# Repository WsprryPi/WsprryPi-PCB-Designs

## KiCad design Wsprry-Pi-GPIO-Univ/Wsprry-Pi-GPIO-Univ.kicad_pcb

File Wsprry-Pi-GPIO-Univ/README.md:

# Wsprry Pi GPIO Board

GPIO transmission board.

## Project files

Open [Wsprry-Pi-GPIO-Univ.kicad_pro](Wsprry-Pi-GPIO-Univ.kicad_pro) in KiCad 10.0.1 or newer. The [schematic PDF](Wsprry-Pi-GPIO-Univ.pdf) is a reference export; the KiCad sources are authoritative.

The [project libraries](libraries/README.md) contain every symbol and footprint used by the design, plus available 3D models. Keep the `libraries/` folder and library tables with the project; their `${KIPRJMOD}` paths resolve within this directory. Library documentation covers connector options, model limitations, sources, and licenses.

## Assembly

C11 is [Panasonic EEEFK1V470P, 47 µF / 35 V](https://www.lcsc.com/product-detail/C178565.html), matching the `C178565` purchasing field, schematic value, and PCB value. Its local footprint uses KiCad's generic `CP_Elec_6.3x5.8` STEP model for visualization; verify the selected part and assembled height mechanically rather than treating the model as physical-fit evidence.

J83 is the locally stored Adafruit 1865 edge-launch SMA connector, with signal on pin 1 and ground on pin 2. It is hand-soldered and excluded from the BOM and position files. The nearby RF route was revised and the conflicting local fence vias were removed; the surrounding ground-via fence remains in place.

Headers J11, J21, J81, and J82 remain part of the electrical design but are excluded from the BOM. Treat them as separately supplied assembly hardware.

## Validation

The design was checked with KiCad 10.0.1 after the edge-connector and 3D-model changes. Run ERC and DRC again after later design edits and before producing manufacturing files.

- ERC: no errors and 1 unconnected-wire-endpoint warning.
- DRC: zero violations, unconnected pads, or schematic-parity errors.

The macOS `kicad-cli pcb drc` launcher aborted in KiCad's UI-registration path during this review, so the reported DRC result comes from the native PCB Editor with zone refill and schematic parity enabled. Board parsing, STEP export, and 3D rendering completed successfully.

The project settings include ignored ERC/DRC categories. These checks do not establish assembly fit or electrical/RF performance. Treat the design as untested until revision-specific physical validation is documented. See the [repository conventions](../README.md) and [validation requirements](../CONTRIBUTING.md).

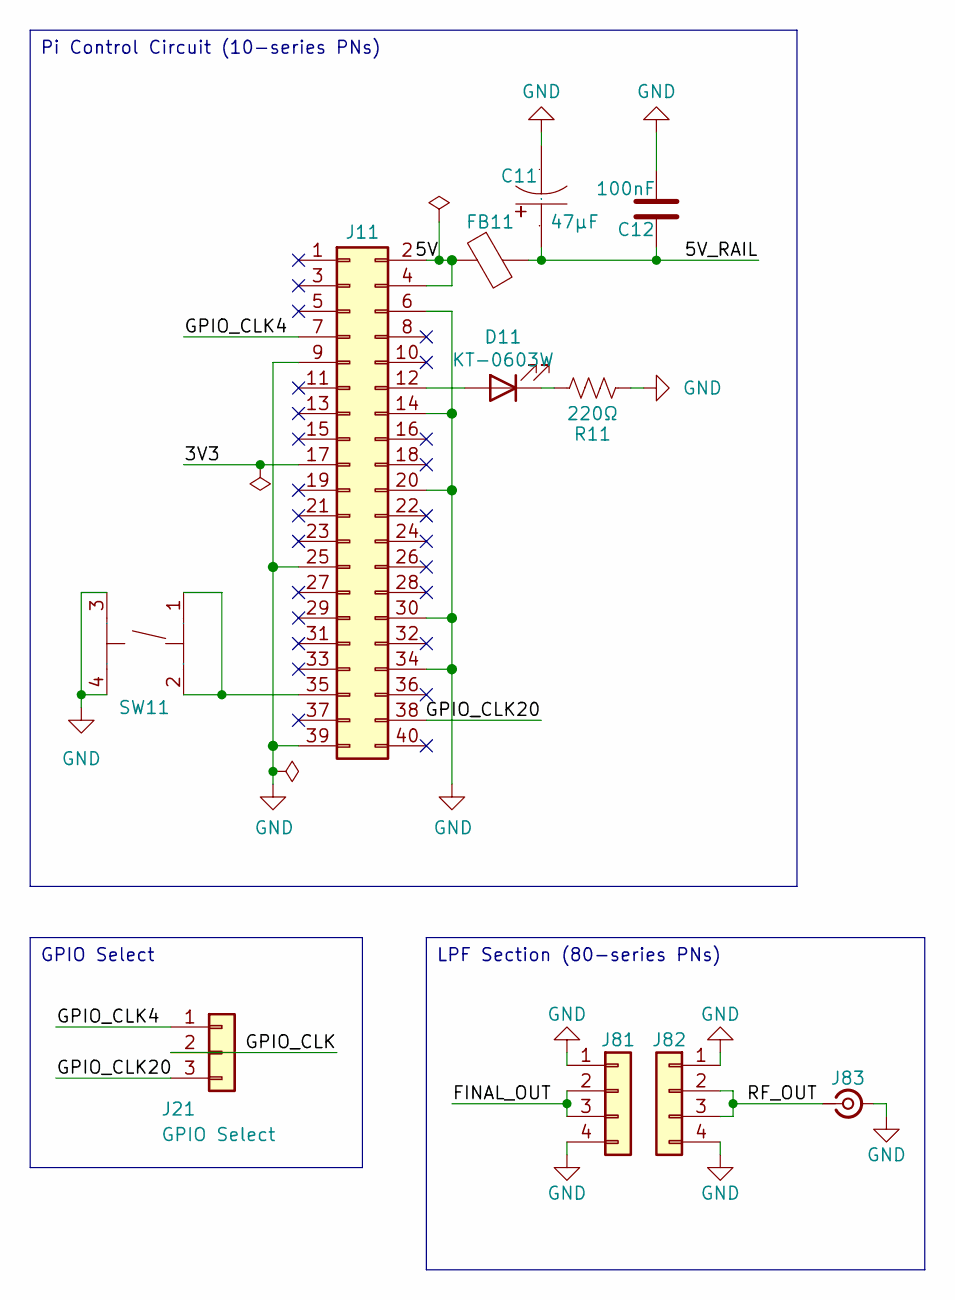
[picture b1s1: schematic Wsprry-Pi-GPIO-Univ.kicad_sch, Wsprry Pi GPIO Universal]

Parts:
C11: 47µF; CAP-SMD_BD6.3-L6.6-W6.6-FD; LCSC_PART C178565
C12: 100nF; C_0603_1608Metric; LCSC_PART C14663
D11: KT-0603W; LED_0603_1608Metric; LCSC_PART C2286
FB11: 600Ω@100MHz; L_0603_1608Metric; LCSC_PART C107335
J11: GPIO; PinSocket_2x20_P2.54mm_Vertical; LCSC_PART C2977589
J21: GPIO Select; PinHeader_1x03_P1.00mm_Vertical
J81, J82: Conn_01x04; PinSocket_1x04_P2.54mm_Vertical; LCSC_PART C2718488
J83: SMA_Adafruit_1865; SMA_Adafruit_1865_EdgeMount; MPN 1865
R11: 220Ω; R_0603_1608Metric; LCSC_PART C22962
SW11: Switch; SW-SMD_4P-L5.1-W5.1-P3.70-LS6.5-TL_H1.5; LCSC_PART C318884

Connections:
/3V3: J11.17
/5V: FB11.1, J11.2, J11.4
/5V_RAIL: C11.1, C12.1, FB11.2
/FINAL_OUT: J81.2, J81.3
/GPIO_CLK: J21.2
/GPIO_CLK4: J11.7, J21.1
/GPIO_CLK20: J11.38, J21.3
/RF_OUT: J82.2, J82.3, J83.1 (In)
GND: C11.2, C12.2, J11.6, J11.9, J11.14, J11.20, J11.25, J11.30, J11.34, J11.39, J81.1, J81.4, J82.1, J82.4, J83.2 (GND), R11.1, SW11.3 (C), SW11.4 (D)
unnamed: D11.2 (A), J11.12
unnamed: D11.1 (K), R11.2
unnamed: J11.35, SW11.1 (A), SW11.2 (B)

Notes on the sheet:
GPIO Select
Pi Control Circuit (10-series PNs)
LPF Section (80-series PNs)

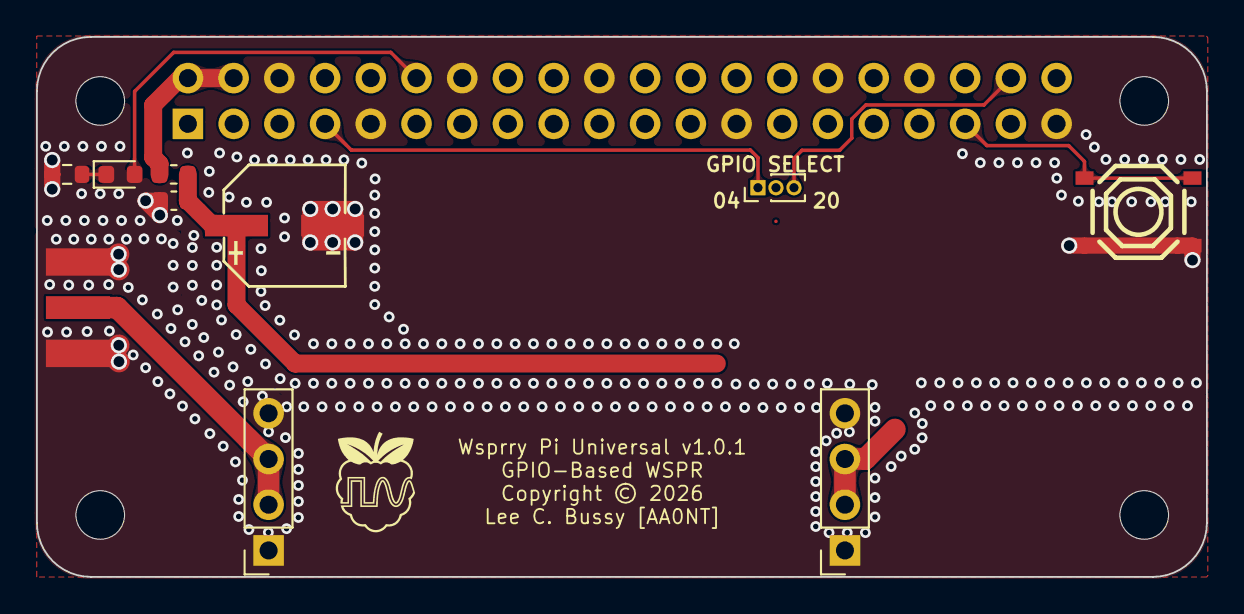
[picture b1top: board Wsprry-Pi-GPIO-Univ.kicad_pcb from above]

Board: 2 copper layers, 65.0 x 30.0 mm, 15 parts (1 on the bottom side), 10 nets.

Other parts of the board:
MH1, MH2, MH3, MH4: MountingHole_2.7mm_M2.5

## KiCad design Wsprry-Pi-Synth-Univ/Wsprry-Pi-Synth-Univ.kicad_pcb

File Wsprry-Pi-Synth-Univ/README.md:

# Wsprry Pi Synth Board

Si5351-synthesized transmission board.

## Project files

Open [Wsprry-Pi-Synth-Univ.kicad_pro](Wsprry-Pi-Synth-Univ.kicad_pro) in KiCad 10.0.1 or newer. The [schematic PDF](Wsprry-Pi-Synth-Univ.pdf) is a reference export; the KiCad sources are authoritative.

The [project libraries](libraries/README.md) contain every symbol and footprint used by the design, plus available 3D models. Keep the `libraries/` folder and library tables with the project; their `${KIPRJMOD}` paths resolve within this directory. Library documentation covers connector options, model limitations, sources, and licenses.

## Assembly

**Resolve C11 before ordering:** the schematic and PCB specify 100 µF, but the `C178565` purchasing fields select [Panasonic EEEFK1V470P, 47 µF / 35 V](https://www.lcsc.com/product-detail/C178565.html). The local symbol default describes the 47 µF part.

J83 is a through-hole BWSMA-KWE-Z001 connector ([LCSC C496551](https://www.lcsc.com/product-detail/C496551.html)), with signal on pin 5 and ground on pins 1–4. The local Adafruit 1865 edge-launch option uses signal pin 1 and ground pin 2; using it requires schematic pin mapping and PCB routing changes.

## Validation

The validation baseline is source revision `bc5cba8`, checked with KiCad 10.0.1. Run ERC and DRC again after design edits and before producing manufacturing files.

- ERC: no errors and 2 unconnected-wire-endpoint warnings.
- DRC: zero violations, unconnected pads, or footprint errors.

The project settings include ignored ERC/DRC categories. These checks do not establish assembly fit or electrical/RF performance. Treat the design as untested until revision-specific physical validation is documented. See the [repository conventions](../README.md) and [validation requirements](../CONTRIBUTING.md).

## Design considerations

[Optional GPS frequency calibration for Pi and Pico](../design/GPS-FREQUENCY-CALIBRATION.md) records the selected LS7366R counter and a proposed common 3.3 V circuit for Pi and Pico. It describes CLK2 measurement against GPS PPS, SPI capture readout, benefits, standalone operation and holdover, and an optional external GPSDO reference. The circuit has not been implemented or physically validated.

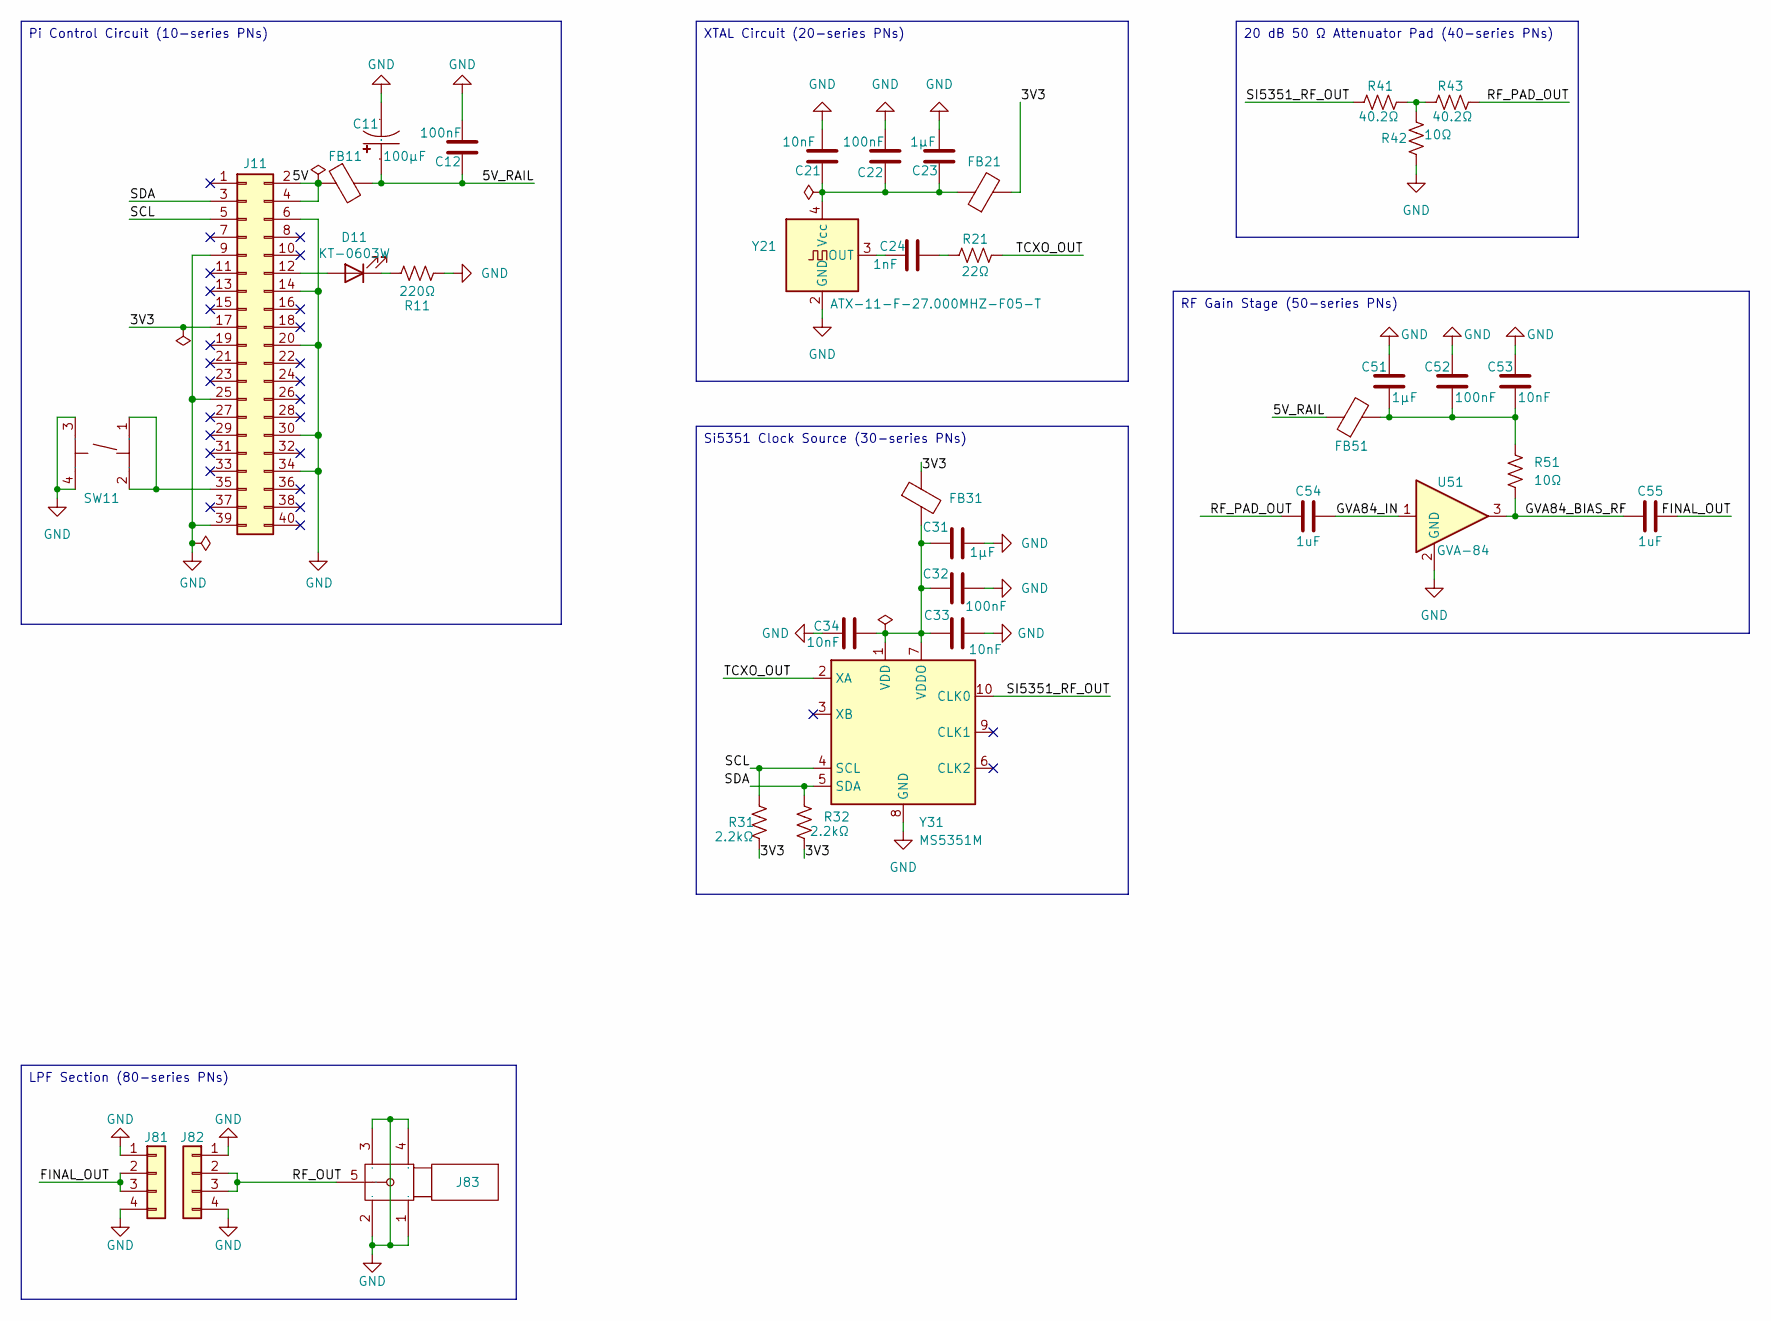
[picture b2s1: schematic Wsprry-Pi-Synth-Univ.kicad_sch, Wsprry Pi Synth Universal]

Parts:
C11: 100µF; CAP-SMD_BD6.3-L6.6-W6.6-FD; LCSC_PART C178565
C12: 100nF; C_0603_1608Metric; LCSC_PART C14663
C21, C33, C34, C53: 10nF; C_0402_1005Metric; LCSC_PART C15195
C22, C32, C52: 100nF; C_0402_1005Metric; LCSC_PART C307331
C23, C31, C51: 1µF; C_0603_1608Metric; LCSC_PART C15849
C24: 1nF; C_0402_1005Metric; LCSC_PART C1523
C54, C55: 1uF; C_0805_2012Metric; LCSC_PART C28323
D11: KT-0603W; LED_0603_1608Metric; LCSC_PART C2286
FB11, FB21, FB31, FB51: 600Ω@100MHz; L_0603_1608Metric; LCSC_PART C107335
J11: GPIO; PinSocket_2x20_P2.54mm_Vertical; LCSC_PART C2977589
J81, J82: Conn_01x04; PinSocket_1x04_P2.54mm_Vertical; LCSC_PART C2718488
J83: SMA; SMA-TH_BWSMA-KWE-Z001; Manufacturer Part BWSMA-KWE-Z001; LCSC_PART C496551
R11: 220Ω; R_0603_1608Metric; LCSC_PART C22962
R21: 22Ω; R_0402_1005Metric; LCSC_PART C25092
R31, R32: 2.2kΩ; R_0402_1005Metric; LCSC_PART C25879
R41, R43: 40.2Ω; R_0603_1608Metric; LCSC_PART C705775
R42: 10Ω; R_0603_1608Metric; LCSC_PART C217691
R51: 10Ω; R_0805_2012Metric; LCSC_PART C17415
SW11: Switch; SW-SMD_4P-L5.1-W5.1-P3.70-LS6.5-TL_H1.5; LCSC_PART C318884
U51: GVA-84; SOT-89-3; LCSC_PART C5445191
Y21: ATX-11-F-27.000MHZ-F05-T; Oscillator_SMD_SeikoEpson_TG2520SMN-xxx-xxxxxx-4Pin_2.5x2.0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; LCSC_PART C6508794
Y31: MS5351M; MSOP-10_3x3mm_P0.5mm; LCSC_PART C1509083

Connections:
/3V3: FB21.2, FB31.1, J11.17, R31.1, R32.1
/5V: FB11.1, J11.2, J11.4
/5V_RAIL: C11.1, C12.1, FB11.2, FB51.1
/FINAL_OUT: C55.2, J81.2, J81.3
/GVA84_BIAS_RF: C55.1, R51.2, U51.3
/GVA84_IN: C54.2, U51.1
/RF_OUT: J82.2, J82.3, J83.5
/RF_PAD_OUT: C54.1, R43.2
/SCL: J11.5, R31.2, Y31.4 (SCL)
/SDA: J11.3, R32.2, Y31.5 (SDA)
/SI5351_RF_OUT: R41.1, Y31.10 (CLK0)
/TCXO_OUT: R21.1, Y31.2 (XA)
GND: C11.2, C12.2, C21.1, C22.1, C23.1, C31.1, C32.2, C33.1, C34.1, C51.2, C52.2, C53.2, J11.6, J11.9, J11.14, J11.20, J11.25, J11.30, J11.34, J11.39, J81.1, J81.4, J82.1, J82.4, J83.1, J83.2, J83.3, J83.4, R11.1, R42.1, SW11.3 (C), SW11.4 (D), U51.2 (GND), Y21.2 (GND), Y31.8 (GND)
unnamed: C24.2, R21.2
unnamed: C51.1, C52.1, C53.1, FB51.2, R51.1
unnamed: D11.2 (A), J11.12
unnamed: D11.1 (K), R11.2
unnamed: J11.35, SW11.1 (A), SW11.2 (B)
unnamed: R41.2, R42.2, R43.1
unnamed: C24.1, Y21.3 (OUT)
unnamed: C21.2, C22.2, C23.2, FB21.1, Y21.4 (Vcc)
unnamed: C31.2, C32.1, C33.2, C34.2, FB31.2, Y31.1 (VDD), Y31.7 (VDDO)

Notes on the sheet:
20 dB 50 Ω Attenuator Pad (40-series PNs)
Pi Control Circuit (10-series PNs)
RF Gain Stage (50-series PNs)
Si5351 Clock Source (30-series PNs)
LPF Section (80-series PNs)
XTAL Circuit (20-series PNs)

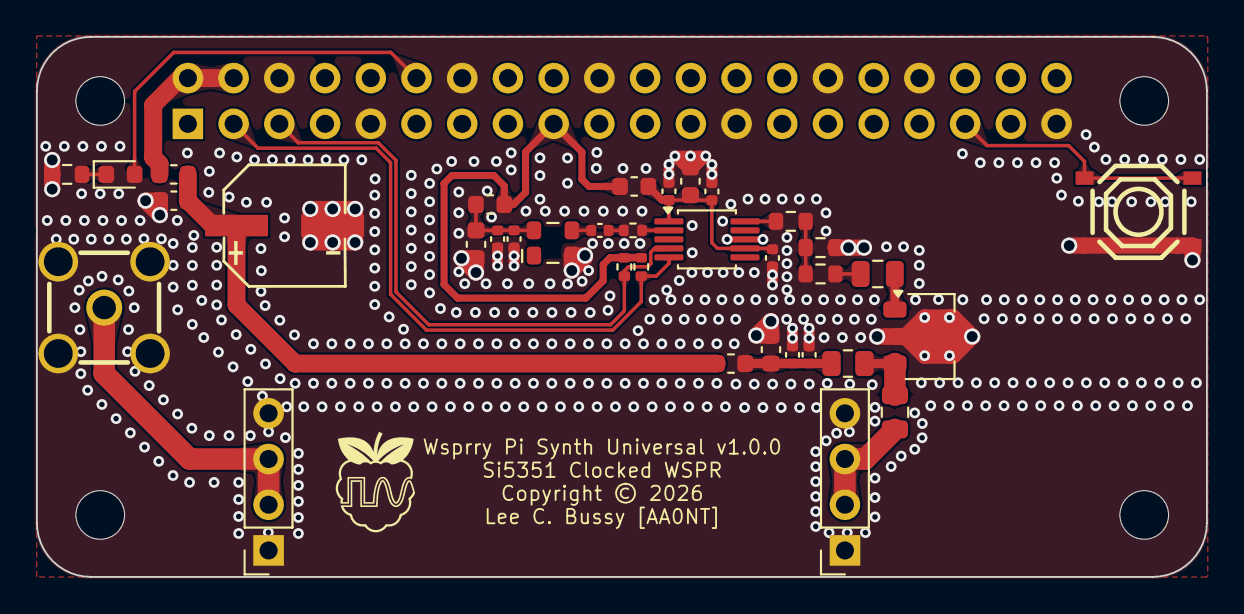
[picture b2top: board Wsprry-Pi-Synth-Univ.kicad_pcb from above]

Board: 2 copper layers, 65.0 x 30.0 mm, 40 parts (1 on the bottom side), 22 nets.

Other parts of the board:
MH1, MH2, MH3, MH4: MountingHole_2.7mm_M2.5

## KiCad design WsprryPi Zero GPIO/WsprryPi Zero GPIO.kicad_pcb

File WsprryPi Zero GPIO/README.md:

# WsprryPi Zero GPIO

A KiCad 10 project initialized from the `RPi Zero HAT` template for WsprryPi GPIO development. It provides the Raspberry Pi Zero-size uHAT geometry, a complete 40-pin GPIO interface, a selectable underside socket model, a socket purchasing item, and independent local libraries.

The schematic and routed two-layer PCB contain the first implementation pass of the 5 V RF amplifier, load-switch circuit, GPIO selection header, LPF interface, and edge-launch SMA output. The design intentionally omits an identification EEPROM and leaves ID_SD and ID_SC unused. Placement and routing are saved, but the board has not been fabricated or physically qualified.

**Cost redesign in progress:** the saved two-transformer LTC6432-15 implementation is too expensive and is no longer the forward design choice. See the [single-BS170 redesign proposal](BS170-REDESIGN-PROPOSAL.md) for the lower-cost candidate and its band-dependent power limits. The proposal has not been applied to the KiCad sources; this routed board remains unsuitable for ordering.

The saved 5 V LTC6432-15 amplifier architecture, its original RF estimate, first-pass BOM, and remaining implementation decisions are recorded in [AMPLIFIER-DESIGN.md](AMPLIFIER-DESIGN.md). It is a new design and does not inherit the earlier 1 W amplifier requirements.

> **Order status: Not ready for order.** The saved implementation uses two Coilcraft `WBC2-1TLC` transformers and an LTC6432-15; it has been rejected on cost grounds. The transformer substitution and the board's electrical/RF performance have not been qualified. The WBC2-1TLC data sheet begins its specified frequency range at 0.2 MHz, above this project's 135 kHz lower target. Do not submit the saved board for fabrication or assembly as the lower-cost design.

## Develop this HAT project

1. Open `WsprryPi Zero GPIO.kicad_pro` in KiCad 10 and review the saved schematic and routed board together.
2. Review the [BS170 redesign proposal](BS170-REDESIGN-PROPOSAL.md) and resolve its open circuit, power, sourcing, and compliance decisions before changing the KiCad sources.
3. After any design change, update the PCB from the schematic as needed, refill copper zones, and rerun ERC and DRC before reviewing the resulting diff.

This project has independent copies of the design files, symbol library, footprint library, and STEP model. Changes here do not update `RPi Zero HAT`, and later template changes do not update this project.

## Schematic block numbering

The schematic is arranged as five boxed functional sections. Circuit parts within those blocks use reference numbers from their section's decade; the prefix distinguishes component types, so a suffix may be reused across types. A few interface and board-only parts retain special references as documented below. Connections within each section are drawn conventionally with wires and explicit branch junctions; net labels are reserved primarily for interfaces between sections and ground references.

| Series | Functional block | References |
| --- | --- | --- |
| 10 | Raspberry Pi HAT interface, GPIO indicator, GPIO-selection header, and socket purchasing item | `U10`, `D11`, `R11`, `J11`, `J12` |
| 20 | GPIO damping, DC blocking, boot-state pull-down, and input transformer | `R20`, `C21`, `R21`, `T21` |
| 30 | LTC6432-15 amplifier, coupling, feedback, noise filtering, and bypassing | `C30`–`C37`, `U31` |
| 40 | Output transformer and grouped J81/J82 LPF interface | `T41`, `J41` |
| 50 | TPS22918 switched 5 V amplifier supply | `U50`, `C51`, `R52`, `C53`, `R54`, `C55` |

J1 is the hand-soldered edge-launch output connector, and H1 is the board-only 3D socket representation; those references sit outside the functional-decade annotation convention. SW11 is the software shutdown-request button in the 10-series. J12 permits GPIO4 or GPIO20 to be jumpered onto `GPIO_RF`. GPIO23 is the active-high `AMP_EN` control, and SW11 grounds GPIO26 for software to detect. GPIO drive-strength selection remains coarse and experimental rather than a calibrated power control.

## Mechanical interface

Coordinates below use the upper-left corner of the 65 × 30 mm board envelope as `(0, 0)`.

| Item | Geometry |
| --- | --- |
| Board envelope | 65 × 30 mm; 1.6 mm thickness; two copper layers |
| Outer corners | 3 mm radius |
| Mounting holes | Four 2.75 mm non-plated holes at `(3.5, 3.5)`, `(61.5, 3.5)`, `(3.5, 26.5)`, and `(61.5, 26.5)` mm |
| Mounting-hole spacing | 58 × 23 mm centers |
| Mounting-hole land | 6.2 mm clear diameter, open solder mask and electrically isolated |
| GPIO interface | Full 2×20 connector, 2.54 mm pitch; pin 1 at `(8.37, 7.31)` mm and pin 2 at `(8.37, 4.77)` mm |
| GPIO extent | Pin columns run from X = 8.37 mm through X = 56.63 mm |
| PoE clearance | Locked 5 × 5 mm underside component-placement keepout at X = 59–64 mm, Y = 7.14–12.14 mm |

U10 combines the 40 GPIO pads and four mechanical holes in one locked footprint. GPIO row orientation follows Raspberry Pi HAT numbering: pin 1 is in the board-interior row and pin 2 is in the board-edge row. The 65 × 30 mm through-hole-header outline is also locked. The connector has an underside courtyard, and the mounting pads enforce the specified copper clearance and solder-mask opening.

The official uHAT drawing allows a 65 × 30.5 mm envelope for an SMT-style through-hole connector arrangement. This project uses a normal through-hole socket and therefore uses the 65 × 30 mm outline.

## Identification and compliance status

This project follows the Raspberry Pi Zero/uHAT mechanical geometry but intentionally omits the identification EEPROM. ID_SD and ID_SC remain unused and must not be repurposed by this design. Because the identification subsystem is omitted, this project does not claim HAT+ compliance.

- Verify STANDBY compatibility: 5 V may be present while 3.3 V is unpowered, and rail sequencing cannot be assumed.
- Select a full 2×20 socket and spacers that provide adequate board-to-board clearance; verify connector, spacer, and component height on every supported Raspberry Pi model.
- Do not back-power the Raspberry Pi unless the design implements the HAT+ power requirements and safe power-path behavior.
- Verify GPIO boot states, contention protection, markings, documentation, and every model-specific mechanical clearance used by the finished design.

## Purchasing BOM

U10 represents the electrical and mechanical interface and is excluded from the purchasing BOM and placement output. J11 is a pinless, schematic-only purchasing symbol for one female 2×20, 2.54 mm socket header; it is excluded from the PCB so schematic-parity DRC does not require a footprint.

The schematic's **Amplifier purchasing BOM** preset exports all parts included in the automated purchasing BOM, including the canonical `LCSC_PART` supplier-ordering field; the legacy `LCSC` field is not used. U10 remains excluded as a non-purchasing interface representation. J11 appears as one row with deliberately blank manufacturer, MPN, and `LCSC_PART` fields because mating height and supported Raspberry Pi models must be chosen for the finished design. Enter the selected socket part before fabrication. J1 is a required hand-soldered SMA connector but is intentionally excluded from BOM and placement output. J12 is also excluded from BOM and placement output by design, while remaining placed for routing and 3D visualization.

The exported BOM is for review of the cost-rejected saved implementation only. It is not an order-ready BOM or a BOM for the proposed BS170 redesign.

## Local libraries and files

Both library tables use the `wsprrypi-zero-gpio` nickname and `${KIPRJMOD}` paths. All required project libraries are inside this directory.

H1 is a separate, selectable footprint that shows the female 2×20 HAT socket on the underside of the board. Delete H1 when the 3D socket is not wanted, or place `wsprrypi-zero-gpio:Raspberry_Pi_HAT_2x20_Socket_3D` to add it back. H1 has no electrical pads and is exempt from the courtyard requirement because it overlays the same physical socket already represented by U10's authoritative underside courtyard. U10 remains the authoritative electrical and mechanical interface, and J11 remains the purchasing item.

The local library includes the grouped 2×4 connector `Dual_PinSocket_1x04_P2.54mm_J81_J82`. Its two 1×4 socket centers are exactly 31.880 mm apart, matching J1/J2 on the current `Wsprry-Pi-LPF` board. Symbol/footprint pins 1–4 correspond to J81 pins 1–4; pins 5–8 correspond to J82 pins 1–4. Its 29.22 × 11.20 mm inter-header rule area prohibits tracks, vias, pads, copper pours, and footprints on `F.Cu` while intentionally allowing the bottom-layer ground pour beneath the LPF. This project-local footprint was adjusted from the Zero HAT template's older 32.020 mm, two-copper-layer definition.

J12 uses the local `Conn_01x03` symbol and `PinHeader_1x03_P2.54mm_Vertical` male through-hole footprint. It is placed and routed with pin 1 on GPIO4, pin 2 on `GPIO_RF`, and pin 3 on GPIO20. The symbol and footprint are excluded from BOM and position output, and the footprint references a project-local STEP model for 3D visualization.

J1 uses the `SMA_Adafruit_1865` symbol and `SMA_Adafruit_1865_EdgeMount` footprint copied from `WsprryPi-GPIO-Univ`. This is the Adafruit 1865 standard-polarity female edge-launch SMA for a 1.6 mm board: pin 1 is signal, pin 2 is ground, the origin is the board seating edge on the signal centerline, and copper extends 0.500–4.064 mm into the board. It is placed and routed, hand-soldered, excluded from BOM and position output, and has no attached 3D model.

The same project-local library contains symbols and assigned footprints for the saved implementation:

- `LTC6432-15`, whose local master and placed U31 metadata select `LTC6432AIUF-15#PBF` and `LCSC_PART` C689344, with the Analog Devices UF24 4 × 4 mm QFN exposed-pad footprint and thermal vias;
- unplaced `YA9308-AEC` with a custom footprint built from Coilcraft's recommended land pattern;
- placed `WBC2-1TLC` on T21 and T41, with `LCSC_PART` C19191658 and a separate custom footprint built from Coilcraft's WBC recommended land pattern; its electrical performance on this board remains unqualified;
- `TPS22918` with the KiCad SOT-23-6 footprint;
- local `R_0603`, `C_0603`, and `C_0805` symbols with local 0603 and 0805 KiCad footprints, plus the project-local `C_1206_3216Metric` footprint assigned in the schematic to C21, C31, C32, C37, and C38; the shared `C_0805` symbol's filter permits both local capacitor footprints while retaining 0805 as its default; `R_0603` uses the compact US zigzag graphic; and
- local `R_US` and `LED` symbols supporting the placed R11 and D11 indicator circuit, with local 0603 footprints and an LED STEP model;
- a project-local `GND` power symbol used by every placed ground-symbol instance;
- the placed `SKRPANE010` momentary tactile switch SW11 for `LCSC_PART` C470426, with an Alps SKRP manufacturer-land-pattern footprint and local STEP model;
- the placed, BOM- and position-output-excluded J12 `Conn_01x03` symbol with a 2.54 mm male through-hole header footprint and local STEP model; and
- the placed, hand-soldered J1 `SMA_Adafruit_1865` symbol with its BOM- and position-output-excluded `SMA_Adafruit_1865_EdgeMount` footprint.

Manufacturer, MPN, `LCSC_PART`, data-sheet, description, and local-footprint fields are embedded in the device symbols where applicable. See [local library sources and licensing](LIBRARY-SOURCES.md) before modifying or redistributing the imported assets.

- [Project settings](WsprryPi%20Zero%20GPIO.kicad_pro): rules, defaults, and BOM preset.
- [Schematic](WsprryPi%20Zero%20GPIO.kicad_sch): proposed five-block amplifier, power-control, and LPF-interface circuit.
- [PCB](WsprryPi%20Zero%20GPIO.kicad_pcb): placed and routed two-layer board with the locked Zero-size outline, interface footprint, mounting-hole lands, PoE keepout, and LPF keepout.
- [Fabrication notes](FABRICATION-NOTES.md): selective U31 via-in-pad fill/cap layer and JLCPCB review instructions.
- [Symbol library](wsprrypi-zero-gpio.kicad_sym): GPIO interface, socket purchasing symbol, and grouped J81/J82 connector symbol.
- [Interface footprint](wsprrypi-zero-gpio.pretty/Raspberry_Pi_Zero_HAT_Interface.kicad_mod).
- [Selectable 2×20 socket footprint](wsprrypi-zero-gpio.pretty/Raspberry_Pi_HAT_2x20_Socket_3D.kicad_mod): board-only 3D representation used by H1.
- [Grouped 2×4 J81/J82 footprint](wsprrypi-zero-gpio.pretty/Dual_PinSocket_1x04_P2.54mm_J81_J82.kicad_mod): exact current LPF-board spacing plus an F.Cu inter-header copper and placement keepout.
- [Local library sources and licensing](LIBRARY-SOURCES.md): imported-footprint provenance, custom-part data sources, license, and validation limits.
- [Local STEP models](wsprrypi-zero-gpio.3dshapes/README.md) for the 2×20 socket, 1×3 male header, 0603 LED, and SKRPANE010 tactile switch.
- [License](LICENSE.md): repository-owned project terms.

The local-library filenames and nickname are unique to this project. Keep generated exports, backups, caches, and local preference files out of this directory.

## Validation and limits

The saved schematic and board are a cost-rejected implementation and are not ready for order. The proposed BS170 redesign, production decisions, and physical/RF qualification remain open. J1, J12, and SW11 are placed; J1 and J12 retain their intentional BOM and placement-output exclusions. The HAT interface footprint keeps its original schematic UUID, so U10 remains associated with the PCB interface when the board is updated from the schematic.

KiCad 10.0.6 schematic ERC reports 0 errors and 0 warnings. KiCad 10.0.6 command-line PCB DRC reports 0 violations, 0 unconnected pads, and 0 footprint errors. These checks do not establish physical assembly, connector fit, Raspberry Pi model compatibility, electrical performance, thermal behavior, or RF performance.

KiCad 10.0.6 successfully exported all 15 project-local symbols and all 15 project-local footprints. The resistor, capacitor, LED, ground, SMA, SKRPANE010, and 1×3 header assets, four device symbols, and two custom RF footprints were visually inspected from those exports. Library inspection, ERC, DRC, routing, and 3D rendering do not establish land-pattern suitability for a particular assembly process, solderability, thermal performance, RF performance, or production readiness.

## Sources and license

The board geometry follows Raspberry Pi's official uHAT mechanical drawing and Raspberry Pi Zero 2 W mechanical drawing. Electrical and compliance notes follow the current HAT+ specification.

The 2×20 socket STEP model derives from the KiCad standard 3D model library and retains the KiCad library license described in the adjacent model notice. The repository MIT license does not replace those third-party terms.

- [Raspberry Pi uHAT mechanical drawing](https://github.com/raspberrypi/hats/blob/master/uhat-board-mechanical.pdf)
- [Raspberry Pi Zero 2 W mechanical drawing](https://pip.raspberrypi.com/documents/RP-008358-DS)
- [Raspberry Pi HAT+ specification](https://datasheets.raspberrypi.com/hat/hat-plus-specification.pdf)
- [KiCad 10 project templates](https://docs.kicad.org/10.0/en/kicad/kicad.html#project_templates)

See [LICENSE.md](LICENSE.md).

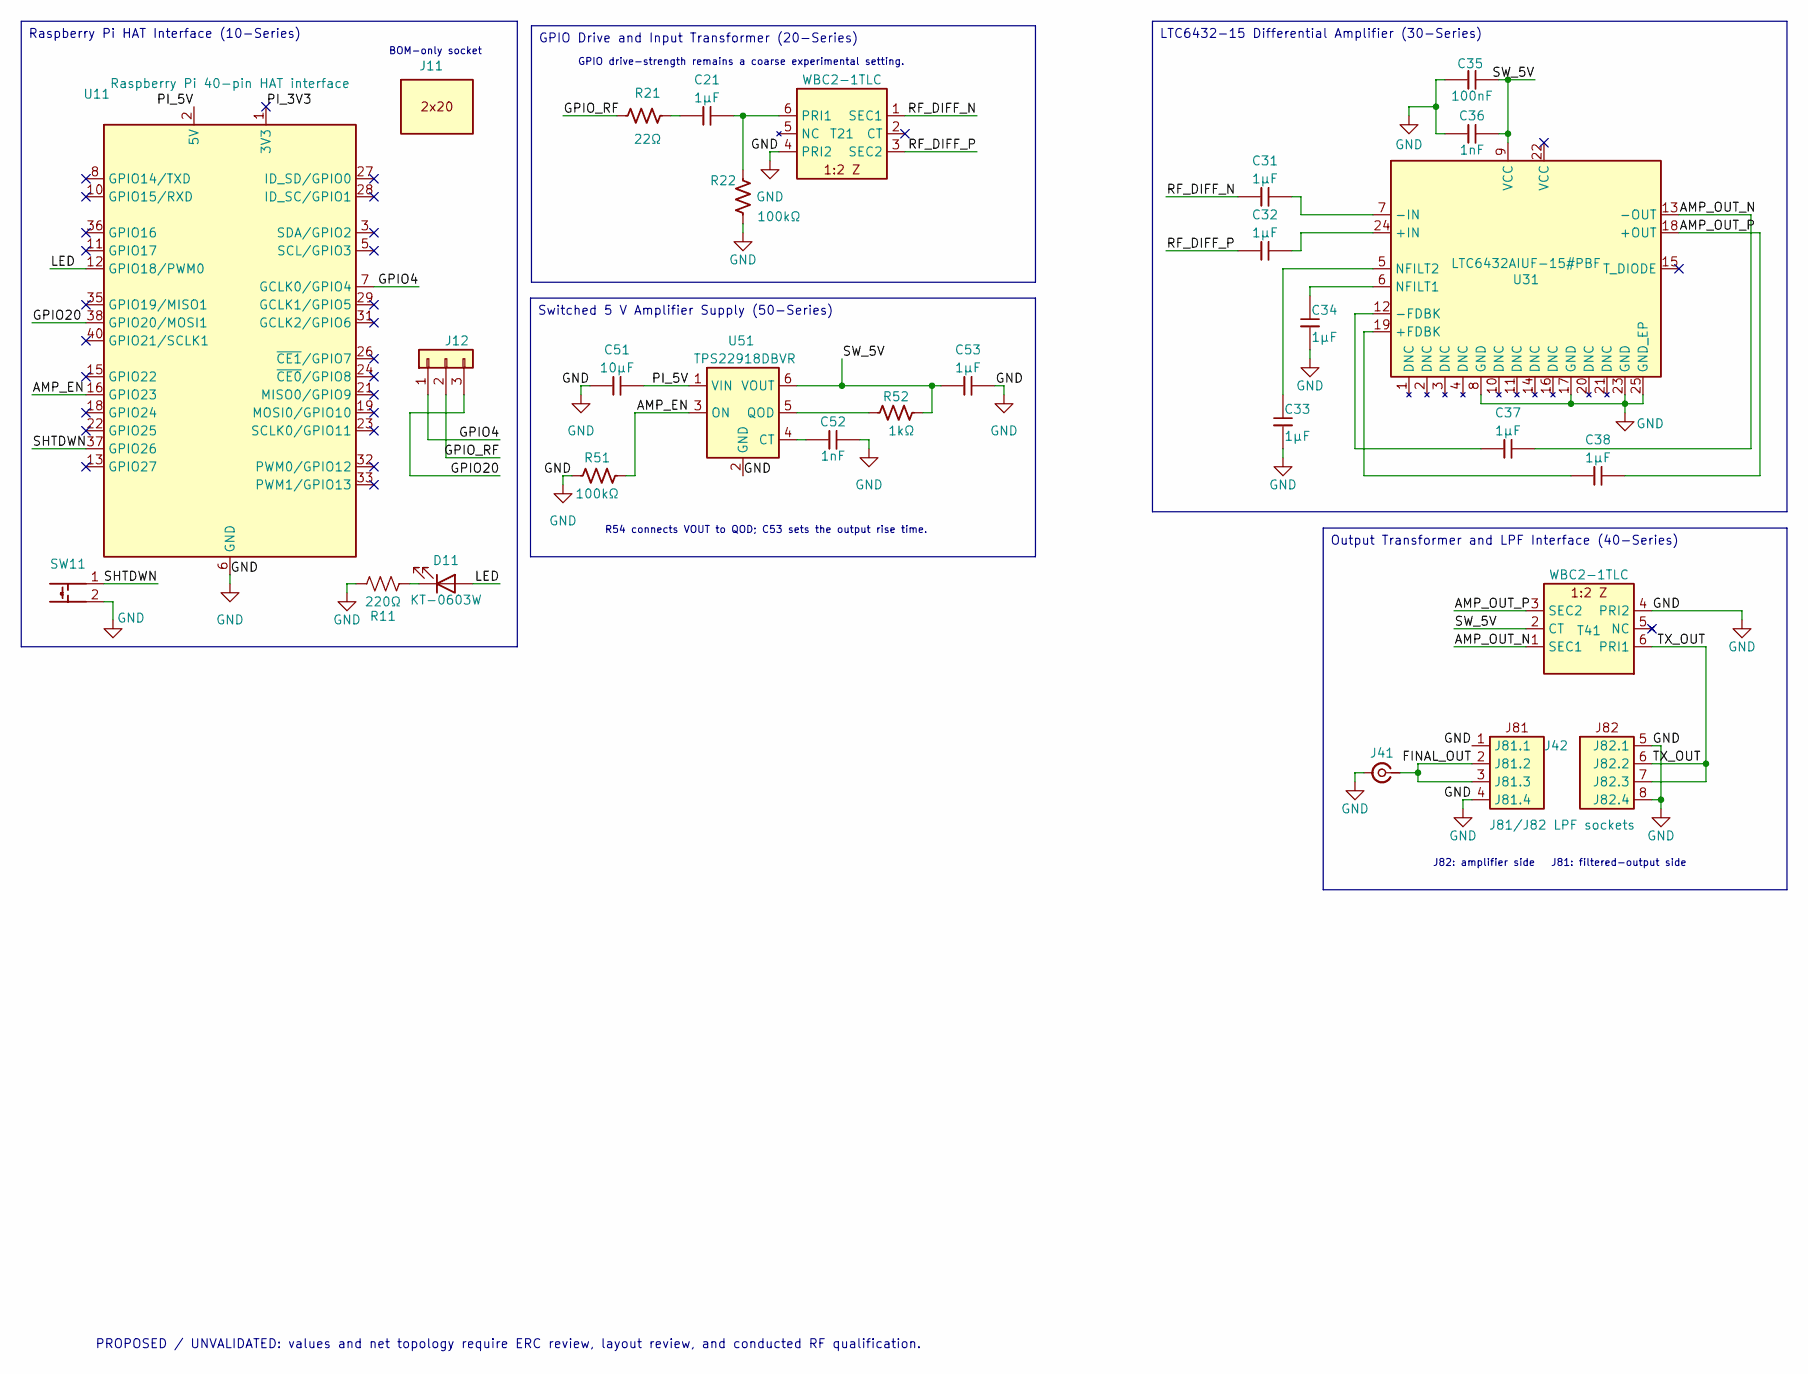
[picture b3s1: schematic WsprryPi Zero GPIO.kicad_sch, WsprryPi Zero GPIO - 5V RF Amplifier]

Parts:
C21, C31, C32, C37, C38: 1µF; C_1206_3216Metric; LCSC_PART C342628
C33, C34, C53: 1µF; C_0805_2012Metric; LCSC_PART C28323
C35: 100nF; C_0603_1608Metric; LCSC_PART C14663
C36, C52: 1nF; C_0603_1608Metric; LCSC_PART C1588
C51: 10µF; C_0805_2012Metric; LCSC_PART C15850
D11: KT-0603W; LED_0603_1608Metric; LCSC_PART C2286
J11: Socket_2x20_P2.54mm
J12: Conn_01x03; PinHeader_1x03_P2.54mm_Vertical
J41: SMA_Adafruit_1865; SMA_Adafruit_1865_EdgeMount; MPN 1865
J42: J81/J82 LPF sockets; Dual_PinSocket_1x04_P2.54mm_J81_J82
R11: 220Ω; R_0603_1608Metric; LCSC_PART C22962
R21: 22Ω; R_0603_1608Metric; LCSC_PART C23186
R22, R51: 100kΩ; R_0603_1608Metric; LCSC_PART C14675
R52: 1kΩ; R_0603_1608Metric; LCSC_PART C2907002
SW11: SKRPANE010; ALPS_SKRP_4.2x3.2mm; MPN SKRPANE010; LCSC_PART C470426
T21, T41: WBC2-1TLC; Coilcraft_WBC2-1TLC; MPN WBC2-1TLC; LCSC_PART C19191658
U11: Raspberry Pi 40-pin HAT interface; Raspberry_Pi_Zero_HAT_Interface
U31: LTC6432AIUF-15#PBF; Analog_UF24_QFN-24-1EP_4x4mm_P0.5mm_EP2.45x2.45mm_ThermalVi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; MPN LTC6432AIUF-15#PBF; LCSC_PART C689344
U51: TPS22918DBVR; SOT-23-6; MPN TPS22918DBVR; LCSC_PART C131941

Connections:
/AMP_EN: R51.1, U11.16 (GPIO23), U51.3 (ON)
/AMP_OUT_N: C37.2, T41.1 (SEC1), U31.13 (-OUT)
/AMP_OUT_P: C38.2, T41.3 (SEC2), U31.18 (+OUT)
/FINAL_OUT: J41.1 (In), J42.2 (J81.2), J42.3 (J81.3)
/GPIO4: J12.1, U11.7 (GCLK0/GPIO4)
/GPIO20: J12.3, U11.38 (GPIO20/MOSI1)
/GPIO_RF: J12.2, R21.1
/LED: D11.2 (A), U11.12 (GPIO18/PWM0)
/PI_5V: C51.2, U11.2 (5V), U11.4 (5V), U51.1 (VIN)
/RF_DIFF_N: C31.1, T21.1 (SEC1)
/RF_DIFF_P: C32.1, T21.3 (SEC2)
/SHTDWN: SW11.1 (A), U11.37 (GPIO26)
/SW_5V: C35.2, C36.2, C53.1, R52.2, T41.2 (CT), U31.9 (VCC), U51.6 (VOUT)
/TX_OUT: J42.6 (J82.2), J42.7 (J82.3), T41.6 (PRI1)
GND: C33.1, C34.1, C35.1, C36.1, C51.1, C52.2, C53.2, J41.2 (GND), J42.1 (J81.1), J42.4 (J81.4), J42.5 (J82.1), J42.8 (J82.4), R11.2, R22.1, R51.2, SW11.2 (B), T21.4 (PRI2), T41.4 (PRI2), U11.6 (GND), U11.9 (GND), U11.14 (GND), U11.20 (GND), U11.25 (GND), U11.30 (GND), U11.34 (GND), U11.39 (GND), U31.8 (GND), U31.17 (GND), U31.23 (GND), U31.25 (GND_EP), U51.2 (GND)
unnamed: C21.1, R21.2
unnamed: D11.1 (K), R11.1
unnamed: C21.2, R22.2, T21.6 (PRI1)
unnamed: C38.1, U31.19 (+FDBK)
unnamed: C32.2, U31.24 (+IN)
unnamed: C37.1, U31.12 (-FDBK)
unnamed: C31.2, U31.7 (-IN)
unnamed: C34.2, U31.6 (NFILT1)
unnamed: C33.2, U31.5 (NFILT2)
unnamed: C52.1, U51.4 (CT)
unnamed: R52.1, U51.5 (QOD)

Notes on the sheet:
GPIO drive-strength remains a coarse experimental setting.
J82: amplifier side J81: filtered-output side
PROPOSED / UNVALIDATED: values and net topology require ERC review, layout review, and conducted RF qualification.
BOM-only socket
R54 connects VOUT to QOD; C53 sets the output rise time.
Output Transformer and LPF Interface (40-Series)
GPIO Drive and Input Transformer (20-Series)
Raspberry Pi HAT Interface (10-Series)
Switched 5 V Amplifier Supply (50-Series)
LTC6432-15 Differential Amplifier (30-Series)

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
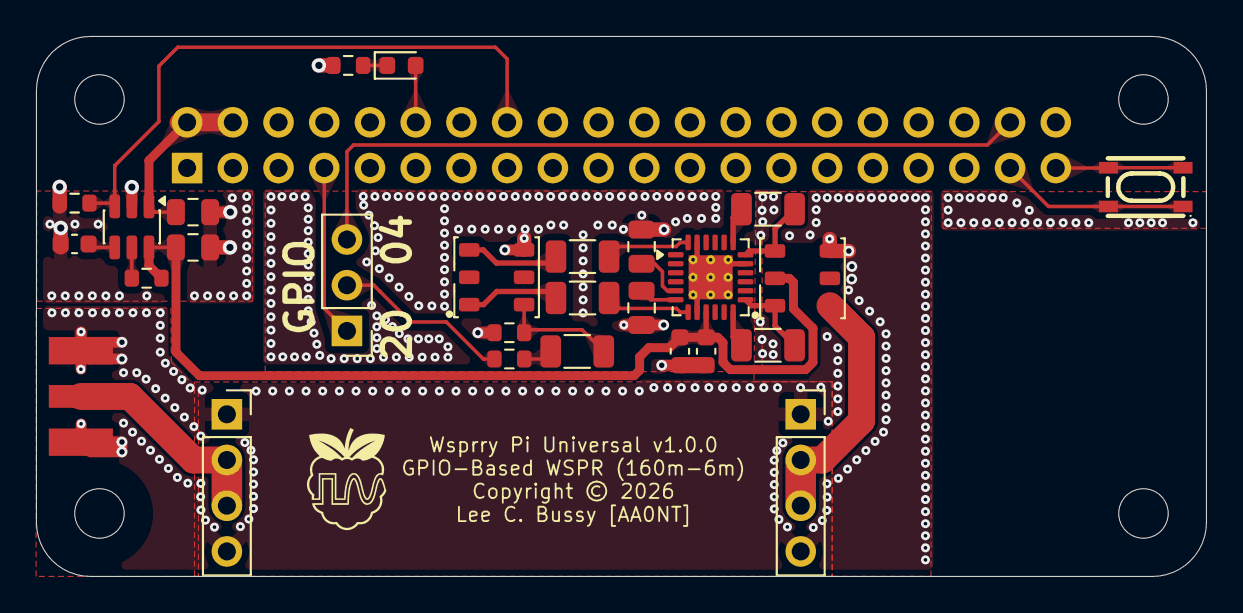
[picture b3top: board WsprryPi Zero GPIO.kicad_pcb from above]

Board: 2 copper layers, 65.0 x 30.0 mm, 28 parts (1 on the bottom side), 26 nets.

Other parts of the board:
H1: Raspberry_Pi_HAT_2x20_Socket_3D

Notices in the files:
Wsprry-Pi-GPIO-Univ/Wsprry-Pi-GPIO-Univ.kicad_pcb:
Copyright © 2026
